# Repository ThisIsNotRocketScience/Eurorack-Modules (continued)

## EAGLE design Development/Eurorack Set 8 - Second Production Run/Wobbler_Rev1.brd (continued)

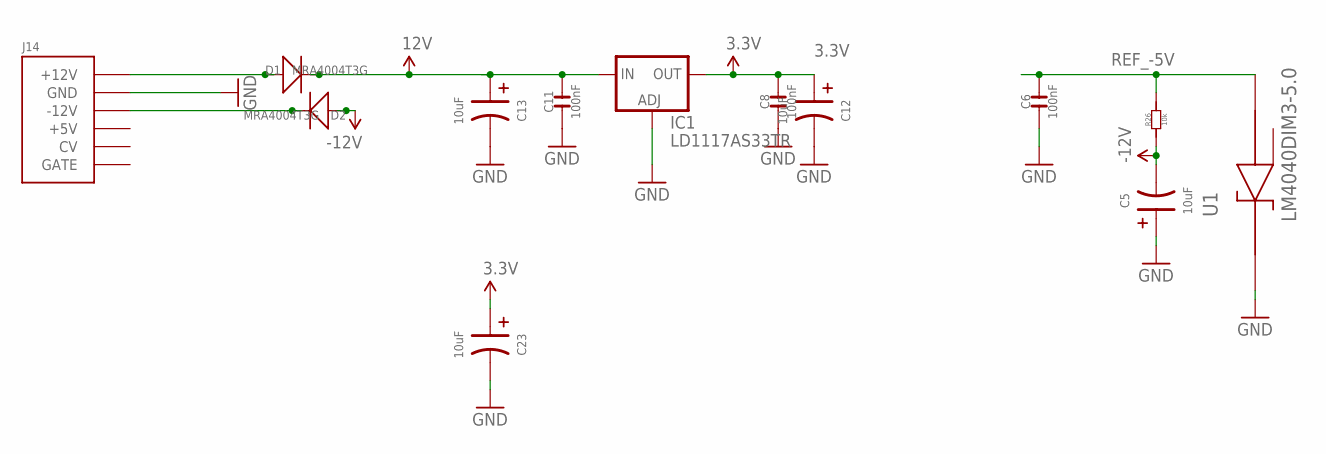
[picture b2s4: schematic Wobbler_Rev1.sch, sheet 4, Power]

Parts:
C5, C12, C13, C23: 10uF; AVX-A; MPN TAJB106K020RNJ
C6: 100nF; C0603; MPN 06035C104KAT2A
C8, C11: 100nF; C0603; MPN MC0603F104Z160CT
D1, D2: MRA4004T3G; DO-214AC; MPN US1G-E3/5AT
IC1: LD1117AS33TR; SOT223; MPN LD1117AS33TR
J14: POWERSMT; 2X08_SMT_HEADER
R26: 10k; R0603
U1: LM4040DIM3-5.0; SOT95P237X112-3N

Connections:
3.3V: C8.2, C12.+ (1), C23.+ (1), IC1.2 (OUT), IC1.4 (OUT); also elsewhere on the board
12V: C11.2, C13.+ (1), D1.2 (-), IC1.3 (IN); also elsewhere on the board
-12V: C5.- (2), D2.1 (+), R26.1; also elsewhere on the board
GND: C5.+ (1), C6.1, C8.1, C11.1, C12.- (2), C13.- (2), C23.- (2), IC1.1 (ADJ), J14.3 (GND), J14.4 (GND), J14.5 (GND), J14.6 (GND), J14.7 (GND), J14.8 (GND), U1.1 (CATHODE); also elsewhere on the board
unnamed: D1.1 (+), J14.9 (+12V), J14.10 (+12V)
unnamed: D2.2 (-), J14.1 (-12V), J14.2 (-12V)
REF_-5V: C6.2, R26.2, U1.2 (ANODE); also elsewhere on the board

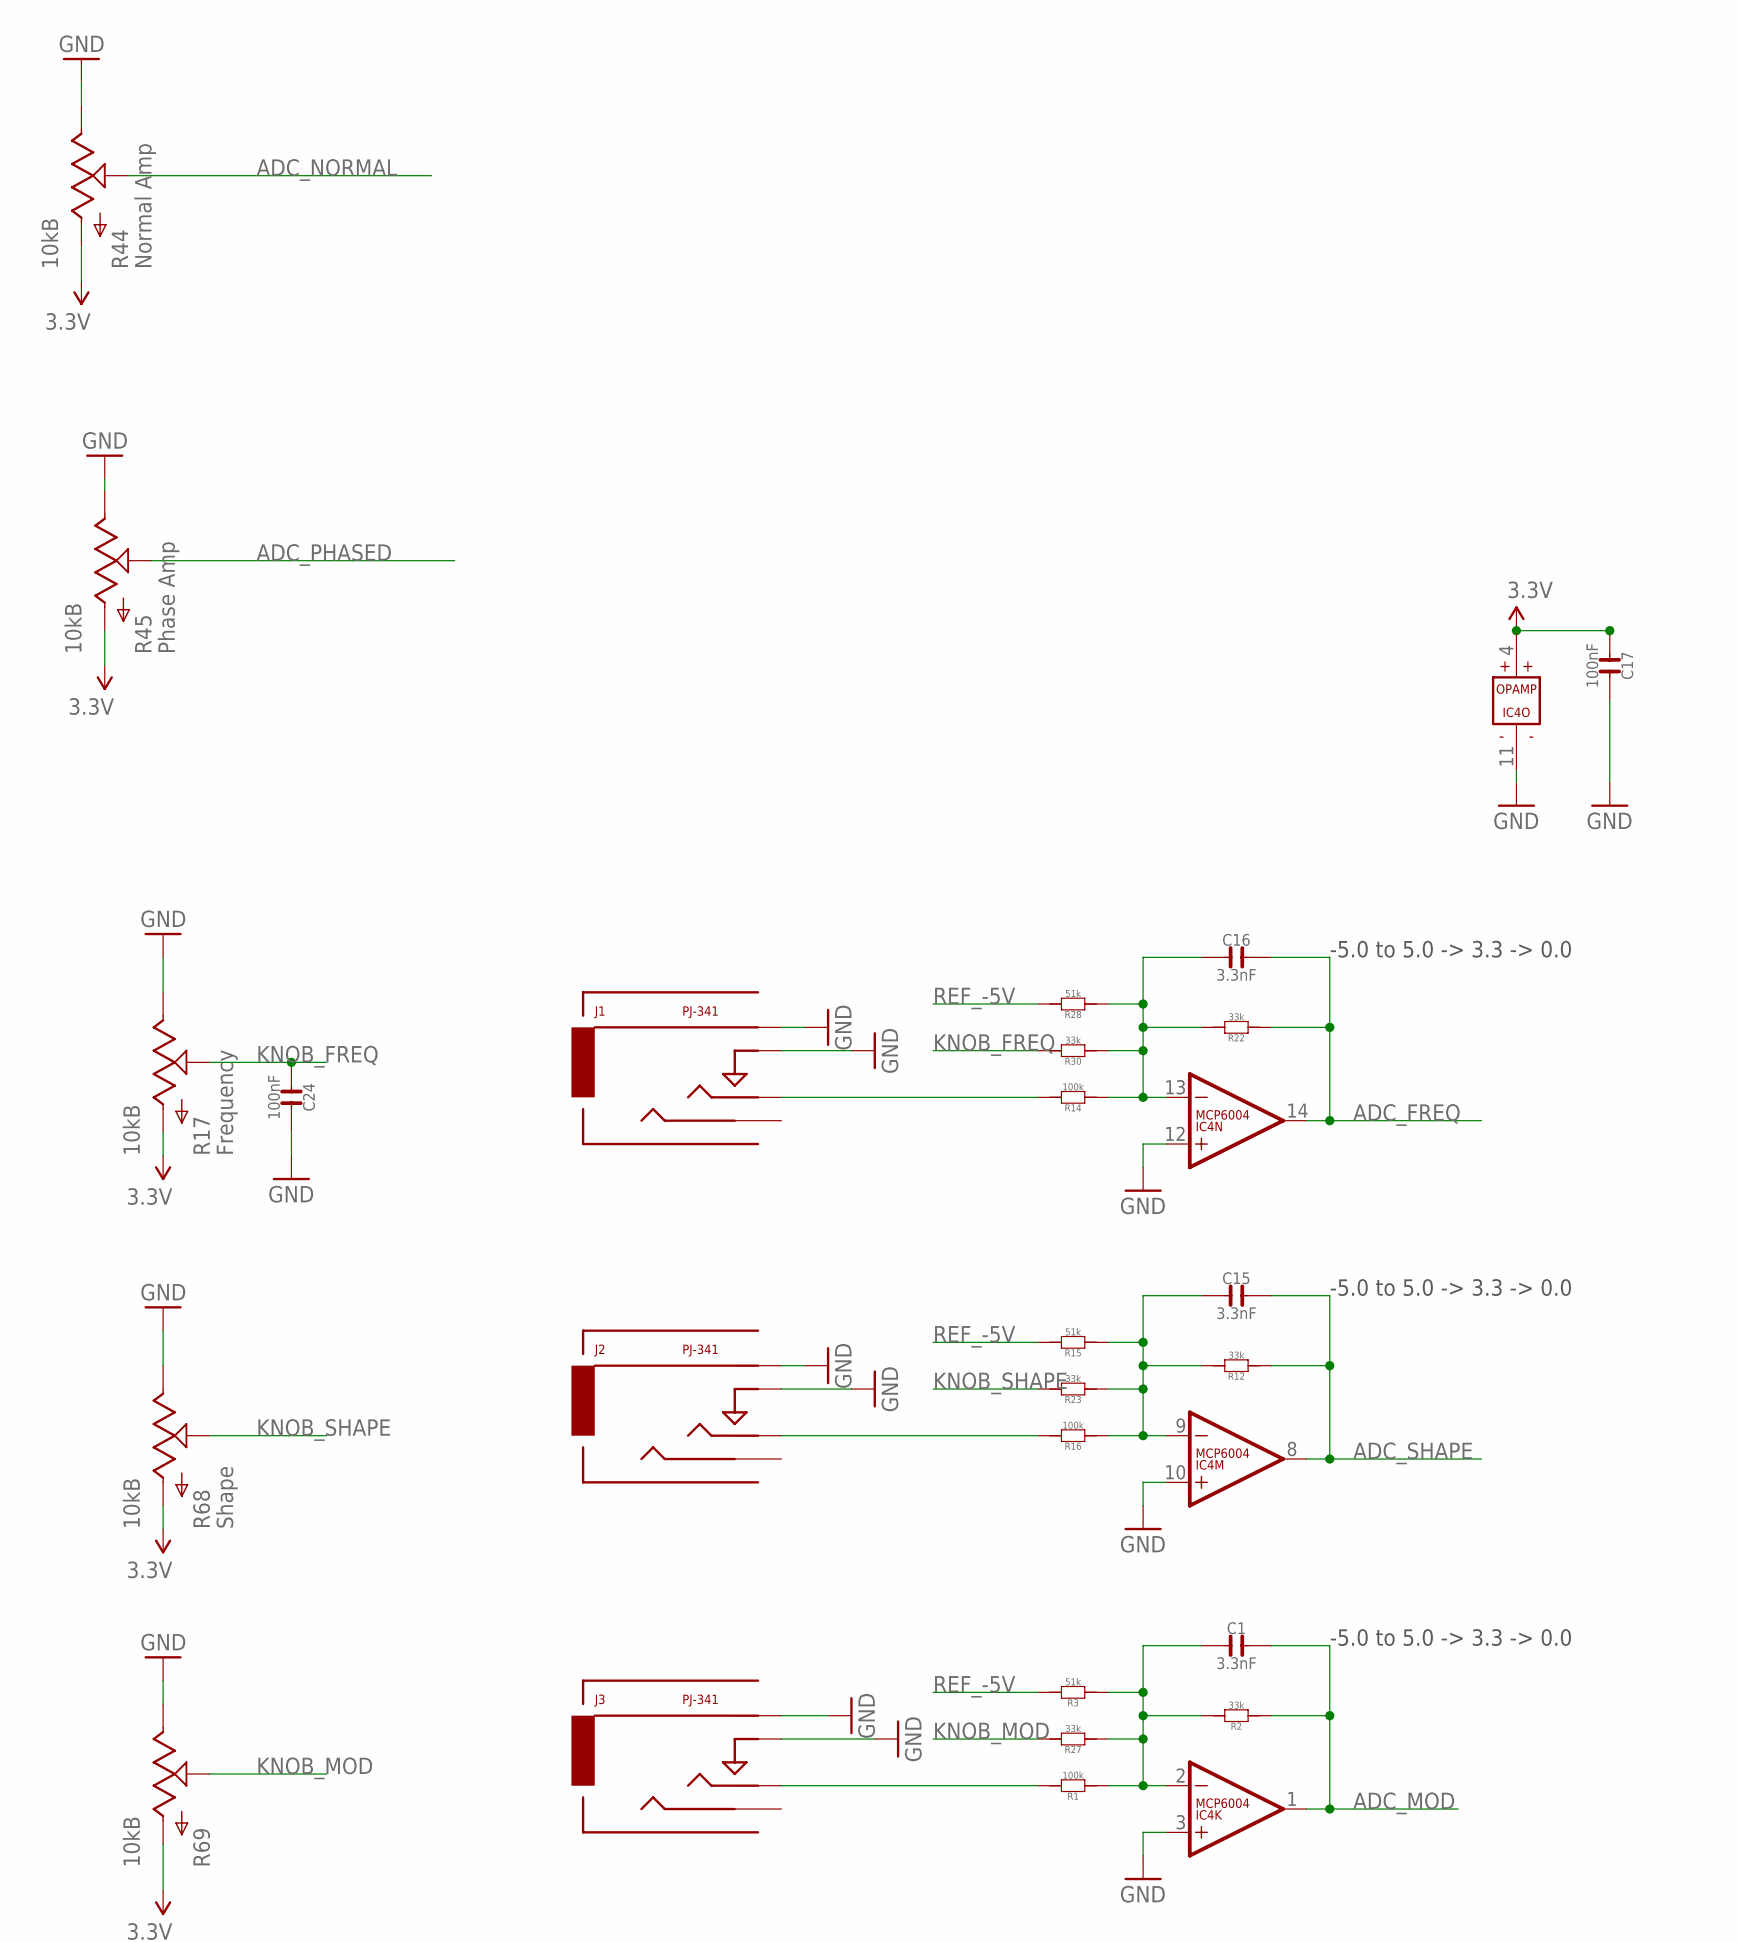
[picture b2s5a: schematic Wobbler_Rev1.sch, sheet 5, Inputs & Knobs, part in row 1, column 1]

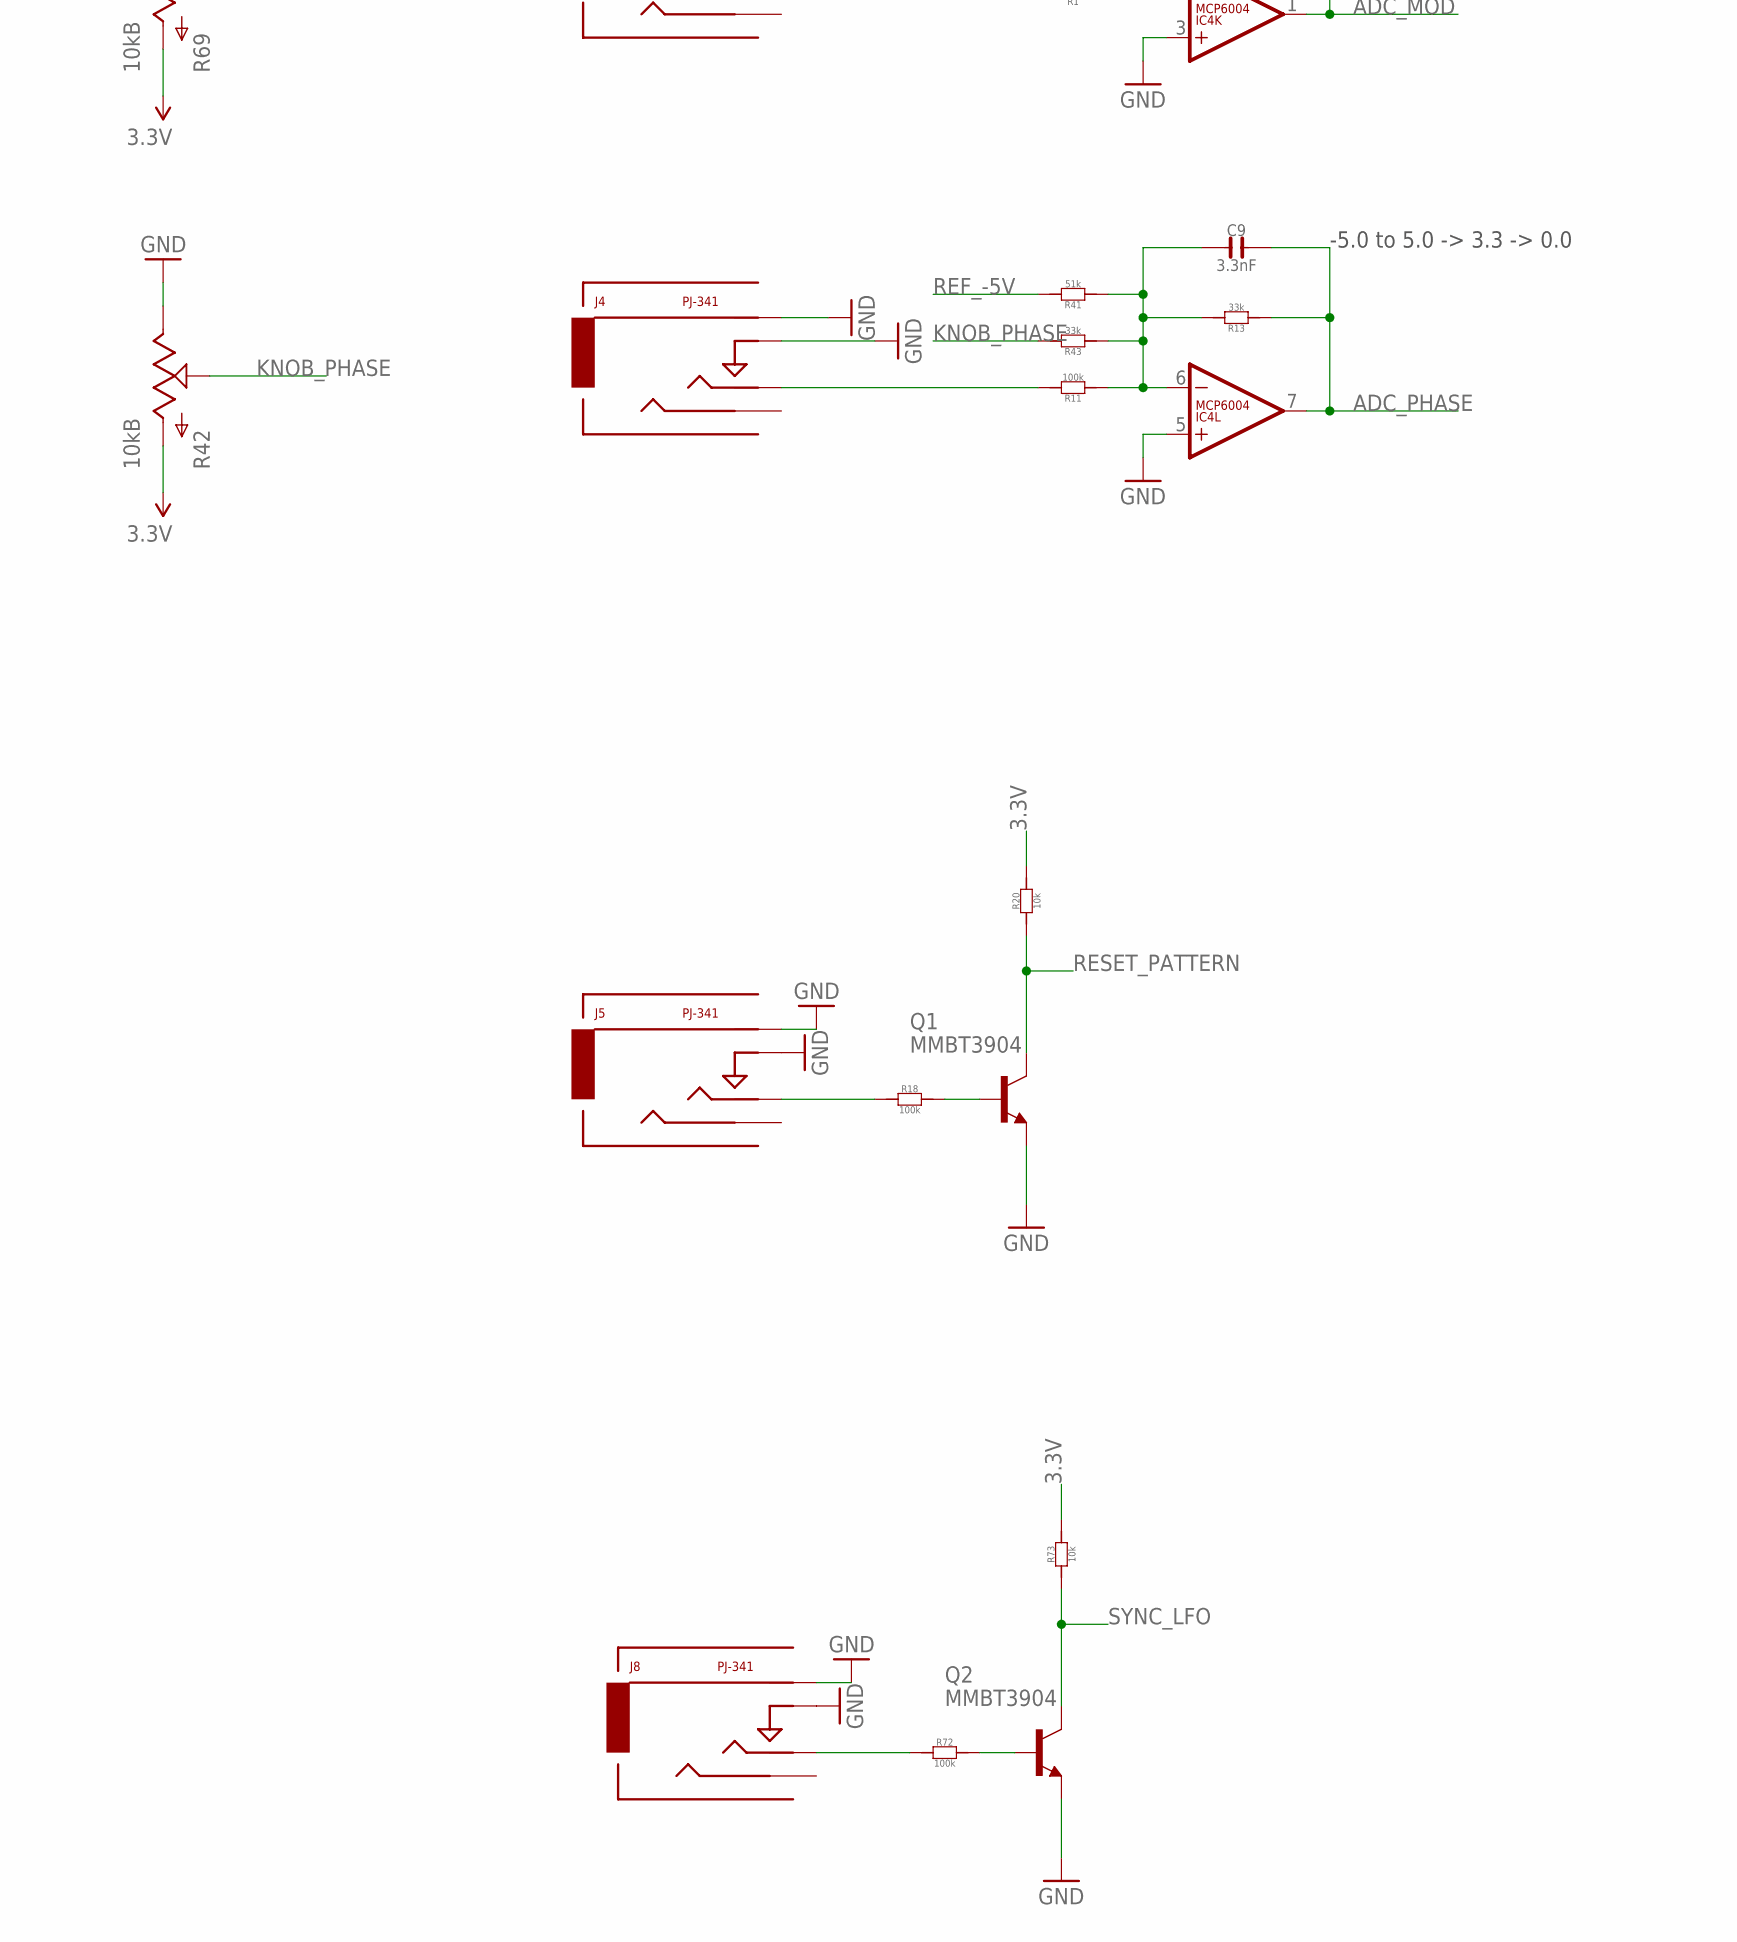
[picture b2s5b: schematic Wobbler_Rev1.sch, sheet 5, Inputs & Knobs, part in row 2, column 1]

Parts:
C1, C9, C15, C16: 3.3nF; C0603
C17, C24: 100nF; C0603; MPN MC0603F104Z160CT
IC4: MCP6004; SO14; MPN MCP6004-I/SL.
J1, J2, J3, J4, J5, J8: PJ-341; 3.5MM-JACK-SWITCH-13MM-INPUT
Q1, Q2: MMBT3904; SOT23-BEC; MPN PMBT3904,215
R1, R11, R14, R16, R18, R72: 100k; R0603
R2, R12, R13, R22, R23, R27, R30, R43: 33k; R0603
R3, R15, R28, R41: 51k; R0603
R17, R42, R44, R45, R68, R69: 10kB; OG-POTS_ALPS_POT_VERTICAL
R20, R73: 10k; R0603

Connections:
3.3V: C17.1, IC4.4 (V+), R17.P$3 (A), R20.2, R42.P$3 (A), R44.P$3 (A), R45.P$3 (A), R68.P$3 (A), R69.P$3 (A), R73.2; also elsewhere on the board
ADC_FREQ: C16.2, IC4.14 (OUT), R22.1; also elsewhere on the board
ADC_MOD: C1.2, IC4.1 (OUT), R2.1; also elsewhere on the board
ADC_NORMAL: R44.P$2 (S); also elsewhere on the board
ADC_PHASE: C9.2, IC4.7 (OUT), R13.1; also elsewhere on the board
ADC_PHASED: R45.P$2 (S); also elsewhere on the board
ADC_SHAPE: C15.2, IC4.8 (OUT), R12.1; also elsewhere on the board
GND: C17.2, C24.2, IC4.3 (+IN), IC4.5 (+IN), IC4.10 (+IN), IC4.11 (V-), IC4.12 (+IN), J1.RING@3 (RING), J1.SWITCH@3 (SWITCH), J2.RING@3 (RING), J2.SWITCH@3 (SWITCH), J3.RING@3 (RING), J3.SWITCH@3 (SWITCH), J4.RING@3 (RING), J4.SWITCH@3 (SWITCH), J5.RING@3 (RING), J5.SWITCH@3 (SWITCH), J8.RING@3 (RING), J8.SWITCH@3 (SWITCH), Q1.E, Q2.E, R17.P$1 (E), R42.P$1 (E), R44.P$1 (E), R45.P$1 (E), R68.P$1 (E), R69.P$1 (E); also elsewhere on the board
KNOB_FREQ: C24.1, R17.P$2 (S), R30.2
KNOB_MOD: R27.2, R69.P$2 (S)
KNOB_PHASE: R42.P$2 (S), R43.2
KNOB_SHAPE: R23.2, R68.P$2 (S)
unnamed: J2.TIP@3 (TIP), R16.2
unnamed: C15.1, IC4.9 (-IN), R12.2, R15.1, R16.1, R23.1
unnamed: J3.TIP@3 (TIP), R1.2
unnamed: C1.1, IC4.2 (-IN), R1.1, R2.2, R3.1, R27.1
unnamed: J4.TIP@3 (TIP), R11.2
unnamed: C9.1, IC4.6 (-IN), R11.1, R13.2, R41.1, R43.1
unnamed: Q1.B, R18.2
unnamed: J5.TIP@3 (TIP), R18.1
unnamed: J1.TIP@3 (TIP), R14.2
unnamed: C16.1, IC4.13 (-IN), R14.1, R22.2, R28.1, R30.1
unnamed: Q2.B, R72.2
unnamed: J8.TIP@3 (TIP), R72.1
REF_-5V: R3.2, R15.2, R28.2, R41.2; also elsewhere on the board
RESET_PATTERN: Q1.C, R20.1; also elsewhere on the board
SYNC_LFO: Q2.C, R73.1; also elsewhere on the board

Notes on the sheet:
-5.0 to 5.0 -> 3.3 -> 0.0

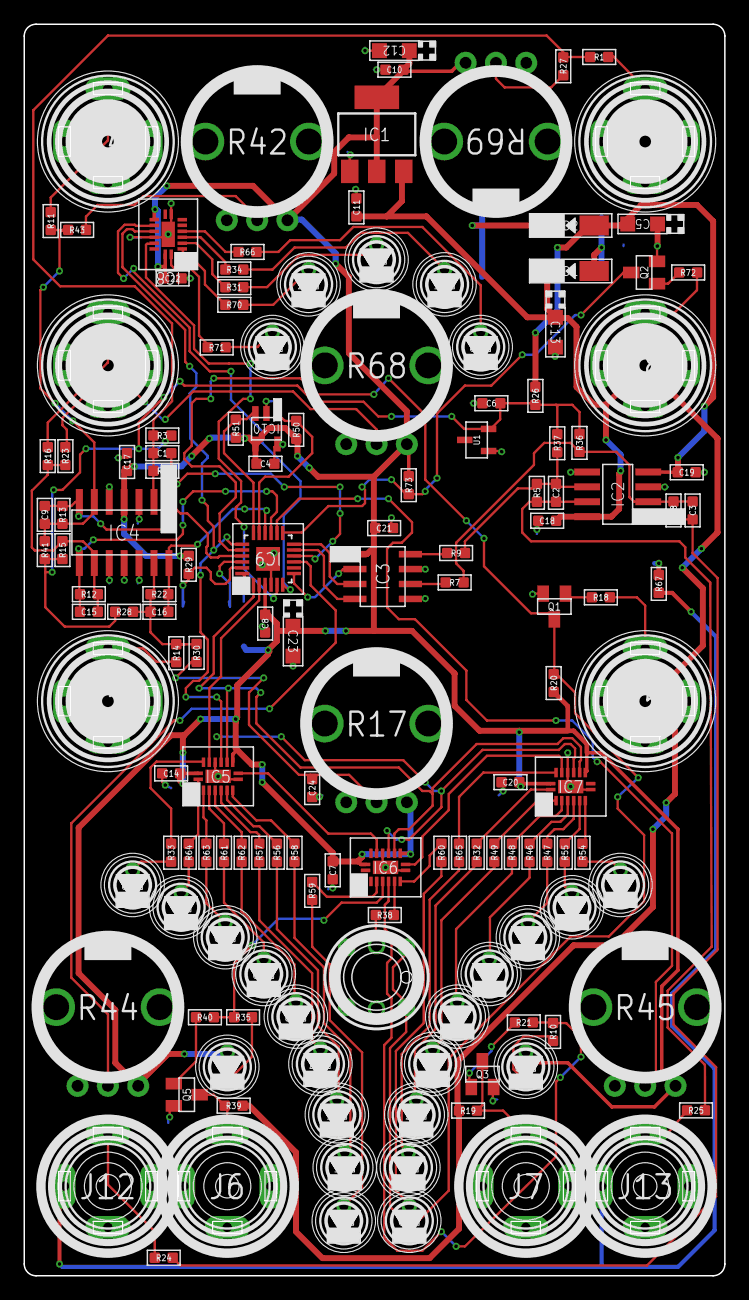
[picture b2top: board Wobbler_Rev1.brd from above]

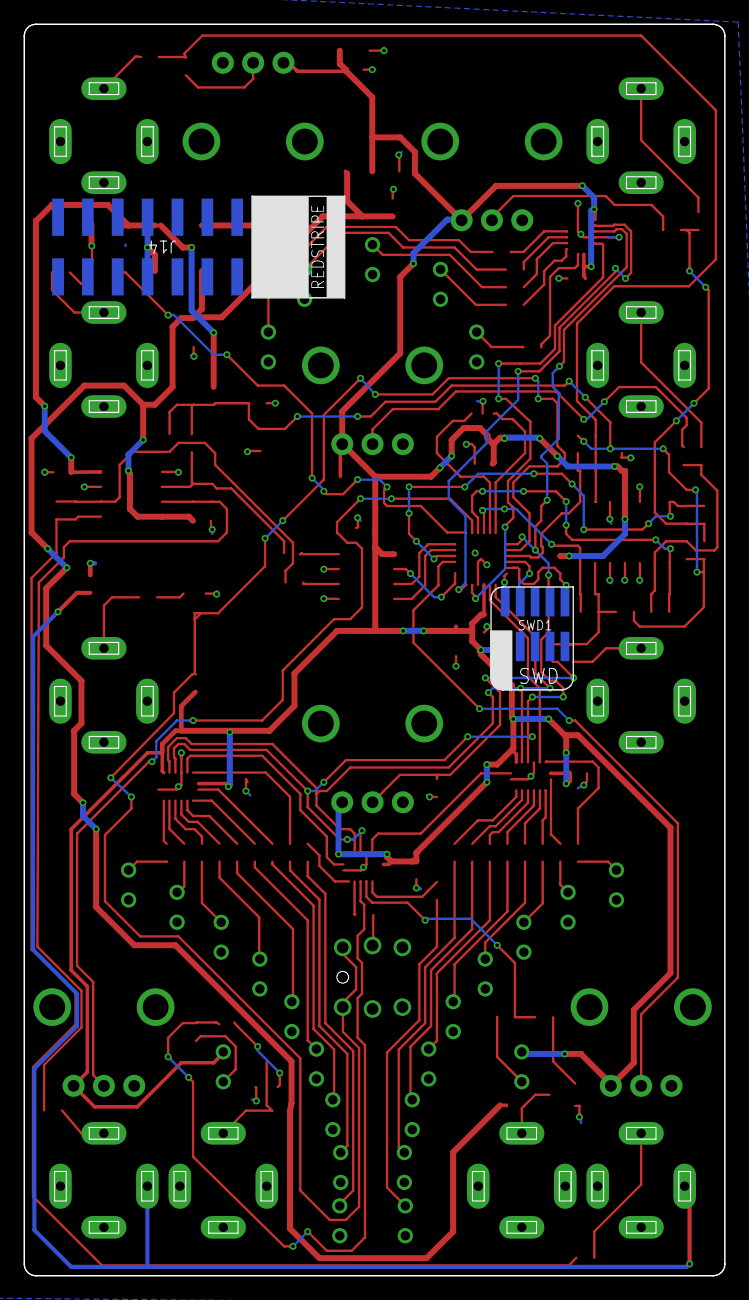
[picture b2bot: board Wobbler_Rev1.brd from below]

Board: 2 copper layers, 59.6 x 106.5 mm, 149 parts (2 on the bottom side), 111 nets.
